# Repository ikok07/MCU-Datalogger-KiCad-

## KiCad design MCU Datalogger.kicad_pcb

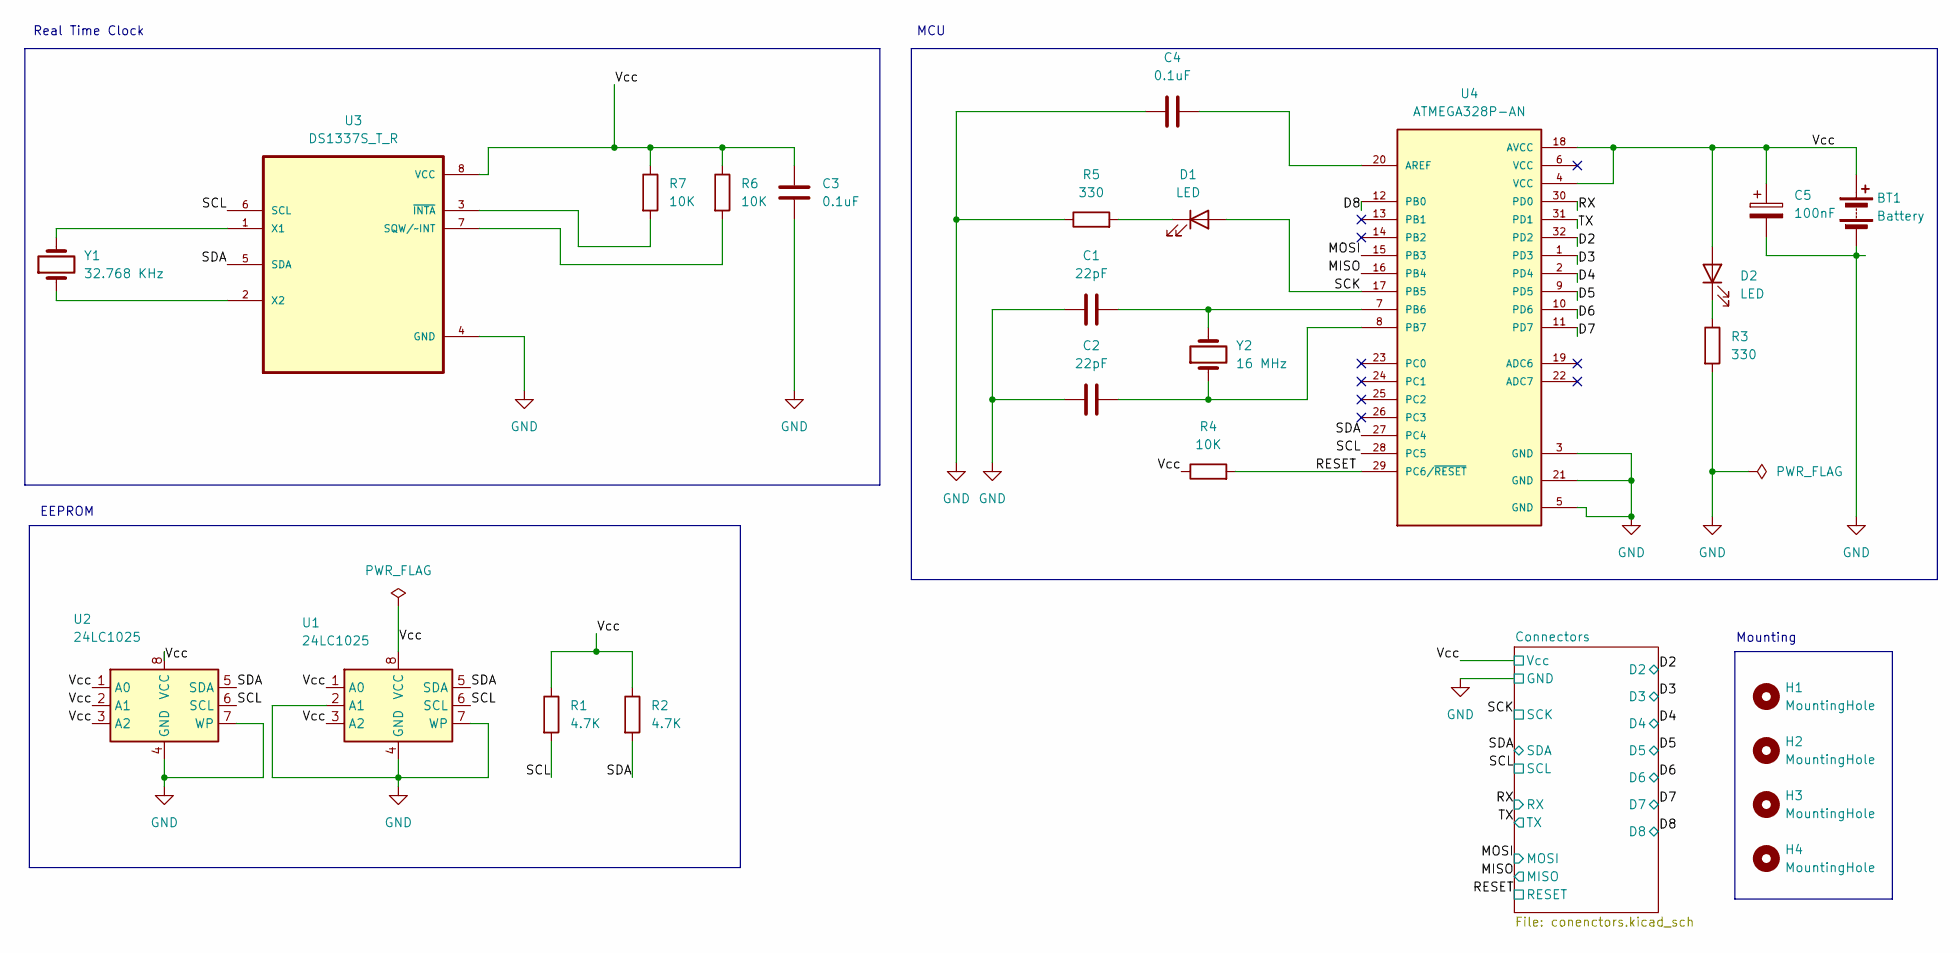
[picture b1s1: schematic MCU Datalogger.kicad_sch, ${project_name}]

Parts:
BT1: Battery; PinHeader_1x02_P2.54mm_Vertical
C1, C2: 22pF; C_0805_2012Metric
C3, C4: 0.1uF; C_0805_2012Metric
C5: 100nF; C_0805_2012Metric
D1, D2: LED; LED_0805_2012Metric
H1, H2, H3, H4: MountingHole; MountingHole_2.1mm
R1, R2: 4.7K; R_0805_2012Metric
R3, R5: 330; R_0805_2012Metric
R4, R6, R7: 10K; R_0805_2012Metric
U1, U2: 24LC1025; SOIC-8_5.23x5.23mm_P1.27mm
U3: DS1337S_T_R; SOIC127P600X175-8N
U4: ATMEGA328P-AN; QFP80P900X900X120-32N
Y1: 32.768 KHz; Crystal_SMD_5032-2Pin_5.0x3.2mm_HandSoldering
Y2: 16 MHz; Crystal_SMD_5032-2Pin_5.0x3.2mm_HandSoldering

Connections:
/D2: U4.32 (PD2); also elsewhere on the board
/D3: U4.1 (PD3); also elsewhere on the board
/D4: U4.2 (PD4); also elsewhere on the board
/D5: U4.9 (PD5); also elsewhere on the board
/D6: U4.10 (PD6); also elsewhere on the board
/D7: U4.11 (PD7); also elsewhere on the board
/D8: U4.12 (PB0); also elsewhere on the board
/MISO: U4.16 (PB4); also elsewhere on the board
/MOSI: U4.15 (PB3); also elsewhere on the board
/RESET: R4.2, U4.29 (PC6/~RESET); also elsewhere on the board
/RX: U4.30 (PD0); also elsewhere on the board
/SCK: D1.2 (A), U4.17 (PB5); also elsewhere on the board
/SCL: R1.2, U1.6 (SCL), U2.6 (SCL), U3.6 (SCL), U4.28 (PC5); also elsewhere on the board
/SDA: R2.2, U1.5 (SDA), U2.5 (SDA), U3.5 (SDA), U4.27 (PC4); also elsewhere on the board
/TX: U4.31 (PD1); also elsewhere on the board
/Vcc: BT1.1 (+), C3.1, C5.1, D2.2 (A), R1.1, R2.1, R4.1, R6.1, R7.1, U1.1 (A0), U1.3 (A2), U1.8 (VCC), U2.1 (A0), U2.2 (A1), U2.3 (A2), U2.8 (VCC), U3.8 (VCC), U4.4 (VCC), U4.18 (AVCC); also elsewhere on the board
GND: BT1.2 (-), C1.1, C2.1, C3.2, C4.1, C5.2, R3.2, R5.1, U1.2 (A1), U1.4 (GND), U1.7 (WP), U2.4 (GND), U2.7 (WP), U3.4 (GND), U4.3 (GND), U4.5 (GND), U4.21 (GND); also elsewhere on the board
unnamed: D1.1 (K), R5.2
unnamed: D2.1 (K), R3.1
unnamed: R6.2, U3.7 (SQW/~INT)
unnamed: U3.1 (X1), Y1.2
unnamed: U3.2 (X2), Y1.1
unnamed: R7.2, U3.3 (~INTA)
unnamed: C4.2, U4.20 (AREF)
unnamed: C1.2, U4.7 (PB6), Y2.2
unnamed: C2.2, U4.8 (PB7), Y2.1

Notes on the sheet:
Real Time Clock
Mounting
EEPROM
MCU

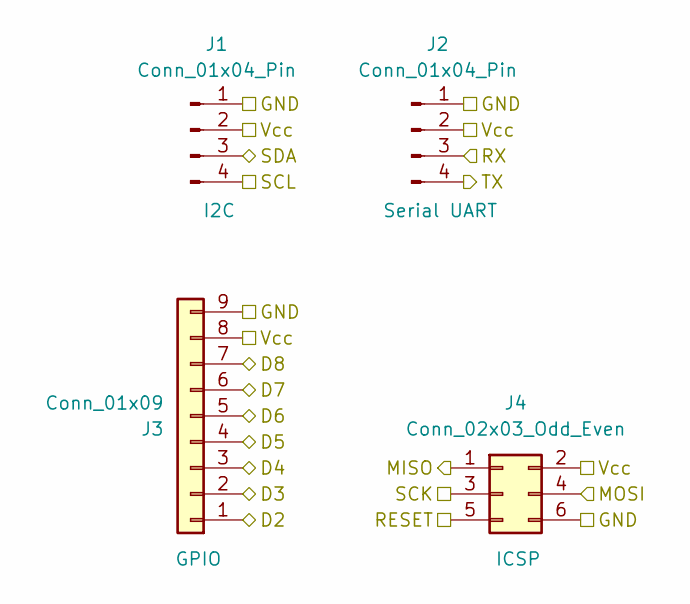
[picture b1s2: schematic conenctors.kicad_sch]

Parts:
J1, J2: Conn_01x04_Pin; PinHeader_1x04_P2.54mm_Vertical
J3: Conn_01x09; PinHeader_1x09_P2.54mm_Vertical
J4: Conn_02x03_Odd_Even; PinHeader_2x03_P2.54mm_Vertical

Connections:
/D2: J3.1; also elsewhere on the board
/D3: J3.2; also elsewhere on the board
/D4: J3.3; also elsewhere on the board
/D5: J3.4; also elsewhere on the board
/D6: J3.5; also elsewhere on the board
/D7: J3.6; also elsewhere on the board
/D8: J3.7; also elsewhere on the board
/MISO: J4.1; also elsewhere on the board
/MOSI: J4.4; also elsewhere on the board
/RESET: J4.5; also elsewhere on the board
/RX: J2.3; also elsewhere on the board
/SCK: J4.3; also elsewhere on the board
/SCL: J1.4; also elsewhere on the board
/SDA: J1.3; also elsewhere on the board
/TX: J2.4; also elsewhere on the board
/Vcc: J1.2, J2.2, J3.8, J4.2; also elsewhere on the board
GND: J1.1, J2.1, J3.9, J4.6; also elsewhere on the board

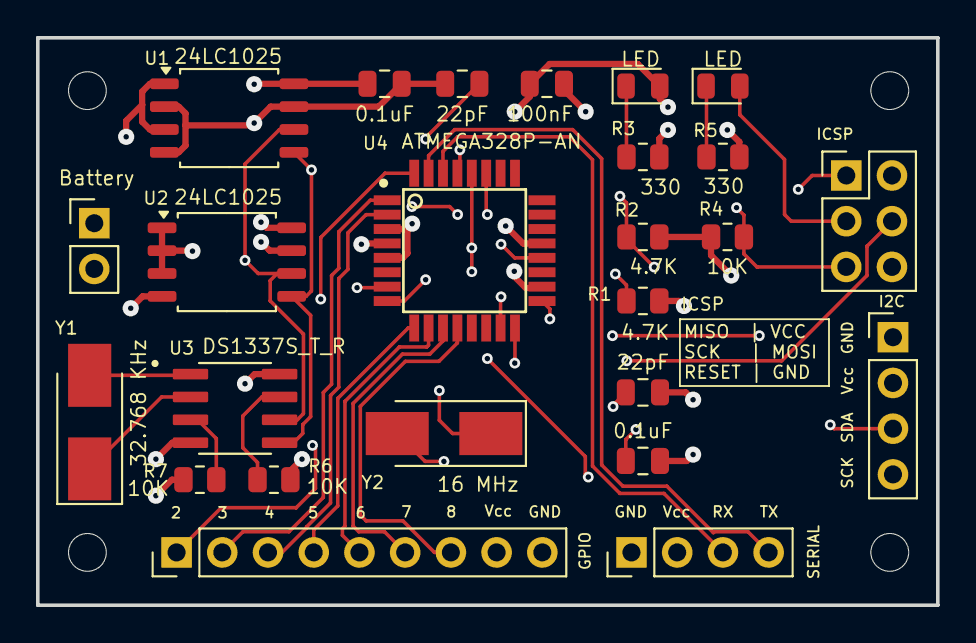
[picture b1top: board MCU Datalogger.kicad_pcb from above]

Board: 4 copper layers, 50.0 x 31.5 mm, 29 parts (0 on the bottom side), 26 nets.

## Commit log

2024-09-19 configure schematic
2024-09-19 arrange schematic symbols
2024-09-19 assign footprints
2024-09-19 wire main scheme sheet
2024-09-19 complete wiring and perform ERC
2024-09-19 add comments
2024-09-20 fix bugs
2024-09-20 setup pcbnew
2024-09-20 place components
2024-09-20 add most of the routes
2024-09-20 fix some routes and add copper fills
2024-09-20 finish the 2-layer pcb
2024-09-20 add unsaved files
2024-09-23 update routes for 4 layer pcb
2024-09-23 update routes for 4-layer pcb
2024-09-23 fix bug in the schematic with SCK and SCL wires
2024-09-23 fix pcb after the schematic bug
2024-09-23 fix pcb after schematic bug (4-layer pcb)
